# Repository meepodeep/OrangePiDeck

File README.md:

# ModuDeck

## A modular cyberdeck that supports multiple SBCS.
  - ### Modules
    - [Exoskeleton](##exoskeleton)
    -   [Compute Modules](##compute) 
        - [Pi 5](###pi-5)
        - [Pi zero 2 w](###pi-zero-2-w)
        - [Lattepanda Mu](###lattepanda-mu)
    - [Battery Modules](##battery)
      - [High Capacity](###2p4s)
      - [Low Capacity](###4s1p)
    - [Keyboard](##keyboard)
    - [Display](##display)
    - [How to assemble modules](##final-assembly)
  - [BOM](#bom) 
## What is the point
I set out to make a modular cyberdeck because I wanted to try to design something that doesnt follow the modern design trends of slimmer and less upgradeable and repairable computers. The modular concept helps alleviate these problems by making use of easily replaceable and upgradeable batteries and SBCs. This also solves the problem of many custom projects being very inconvenient to do maintenance on. For example, some people hotglue everything into place, making the project nearly impossible to work on. In this project, however, every part that you would need to replace is easily replaceable with m3 and m2.5 hardware, securing it in place. 

# Assembly Instructions
- ## Exoskeleton
  - ### Printing
1. Print Both main case peices vertically
2. Print both rear cases flat or vertically if you have elephants foot issues
3. Assemble both sides of each part together using either superglue, plastic welding, or your preferred method of attaching 3d prints.
4. Use m3 hardware to secure the back on once done with wiring exept leave these 3 holes unscrewed, they are for mounting the modules.
5. 
6. 

  - ### Wiring
1. Press fit all of the connectors including, HDMI, XT60, and the magnetic 4pin adafruit connector.

3. Solder the 12v supply for the xt60 on the battery to the 12v supply on the compute xt60 with 18awg wire.
4. Solder the 5v supply for the xt60 on the battery to the 5v supply on the compute xt60 with 18awg wire.

- ## Compute
  - ### Pi 5

1. Print the pi 5 compute model.
2. Assemble the cooler.
3. Solder 28awg wire to the 4 USB pins from the Bottom of the USB 2.0 connector on the set of pins closest to the edge of the board.
4. Remove the casing from the micro HDMI to HDMI adapter.
5. Press the HDMI into the casing.
6. Solder the 5v and gnd connections from the gpio to the + and - terminals onto an xt60 connector using 18awg wire. Press the connector into the 5v part of the module.

7. Press the 5v Xt60 into the case.
8. Solder the other ends of the wires coming from the USB to the magnetic connector in this order, from left to right, on the pin side. Ground, Data+, Data-, Vcc.
9. Press the Magnetic connector into the case.
10. Screw the pi into the mounting posts with m2.5 hardware.
  - ### Pi zero 2 w

1. Print the Pi Zero Compute model.
2. Assemble the cooler
3. Decase the USB hub.
4. Solder 28awg wire to the pins of the USB port at the end of the hub.
5. Solder the other ends of the wires coming from the USB to the magnetic connector in this order, from left to right, on the pin side. Ground, Data+, Data-, Vcc.
6. Press the Magnetic connector into the case.
7. Solder the 5V and GND connections from the GPIO to the + and - terminals onto an xt60 connector using 18awg wire.
8. Press the connector into the 5V part of the module.

9. Decase the mini HDMI adapter on the big HDMI side.
10. Press the HDMI into the case, and plug in the mini HDMI.
11. Screw the pi into the mounting posts with m2.5 hardware.
  - ### Lattepanda mu
1. Print the Lattepanda compute module.
2. Assemble the Panda, cooler, and devboard.
3. Desolder the Barrel jack connector
5. Solder 28awg wire to the 4 USB pins on the bottom of the furthest USB connector from the edge of the board on the port that is covered by the case.

6. Solder 18awg wire to the + and - of the barrel jack and solder them to the + and - of an xt60.
7. Press that into the 12V supply port on the module.
8. Solder the other ends of the wires coming from the USB to the magnetic connector in this order, from left to right, on the pin side. Ground, Data+, Data-, Vcc.
9. Desolder the hdmi port and solder 28awg magnet wire or normal wire onto each pin (i know its annoying) and also to the corresponding pins on the board, make these wires long enough to reach the other side of the case.
10. Press the HDMI port into the case.

- ## Battery
  - ### Build
1. Print battery module cover.
2. Print battery module.
  - ### 2p4s
    - Wiring
- # BEFORE DOING THIS MAKE SURE ALL OF THE CELLS ARE AT THE SAME VOLTAGE SO YOU DONT EXPLODE YOU HOUSE!!
1.  Wire 4 pairs of cells in a 1p configuration by spot welding nickel strips in between the cells.
2.  
3.  Wire all 4 of those 1p cells in series into a 2p4s Configuration by spot welding nickel strips, this is the green section of the diagram.
4.  Solder 5 equal-length wires of 22awg to the BMS and to the parts of the battery; these are the purple wires in the diagram.
5. 
6.  Solder a 12awg wire to the - terminal on the BMS.
7.  Solder a 12awg wire to the + terminal on the BMS and to the power switch, solder another 12awg wire to the other side of said switch, and press it into the case.
8.  
9.  Follow the wiring diagram from step 8 in order to complete the battery, then make sure to insulate all of the connections with your preferred method.
10.  Press both XT60s into their respective ports.
11.  Screw on the top using m3 hardware.
  - ### 4s1p
    - Same as 2p4s, but instead of having cell pairs, just use individual cells. 
- ## Keyboard
- 

1. Solder all of the switches onto the PCB.
2. Solder all of the diodes onto the PCB.
4. Solder the Pi Pico onto the bottom of the PCB.
5. Use [QMK Configurator](https://docs.qmk.fm/configurator_step_by_step) to configure and flash the board [here](https://config.qmk.fm/#/rart/rart75hs/LAYOUT_ansi_split_bs)
6.  Desolder the pi picos usb port.
7. Solder a 28awg wire onto each of the usb pads.
8. Solder the other ends of the wires coming from the USB to the magnetic connector in this order, from left to right, on the pin side vcc, Data-, Data+, Ground.
9. Press the magnetic connector into its slot where the compute module clips in.
10. 
11. Slide the keyboard in and screw it down using m3 hardware.
- ## Display
1. Print both screen mount halves and secure them together using ca plastic welding or your preferred adhesive.
2. Use double-sided tape to secure the driver board to the back of the screen on the left side, away from the compute module.
3. Position the screen in the main case and put the scren mount around it aligned with the screw holes.
4. Screw in m3 hardware from the top of the case in all of the holes.
5. Plug the HDMI coming from the compute module bay into the display board.
6. Use 18awg wire to the 12V XT60 from the battery module bay to the power pads on the driver board after desoldering the barrel plug.
- ## Final Assembly
1. Slot the compute module into the left of the cyberdeck making sure all of the connectors line up.
2. Use 2 m3 bolts to secure the module in place.
3. 
4. Slot the battery in, turned off, into the slot on the right, making sure all of the connectors line up.
5. Screw in one m3 bolt to secure it in place
6. 

# BOM

| Item |	Quantity |	Total price+Shipping | Use In project	| Item Source
| ------------- | ------------- | ------------- | ------------- |------------- |
| General |||||			
| Display |	x1 |	$64.19 |	displays | https://www.ebay.com/itm/145841358470? |
| m3 hardware kit |	x1	| $7.99|	Mount most things	| https://www.amazon.com/Hincell-540pcs-Button-Washers-Stainless/dp/B0D1CV8V9Y?source=ps-sl-shoppingads-lpcontext&ref_=fplfs&smid=A8FI3NPCLLLAU&gQT=2&th=1|
|m2.5 4mm |	x1 |	$1.86 |	mount the pis if you use them |	https://www.aliexpress.us/item/3256805692588351.html?spm=a2g0o.productlist.main.9.70f8PGXgPGXgES&algo_pvid=f41aab01-f6bc-4ebf-8b6a-e709e2d91d9e&algo_exp_id=f41aab01-f6bc-4ebf-8b6a-e709e2d91d9e-8&pdp_ext_f=%7B%22order%22%3A%22141%22%2C%22eval%22%3A%221%22%7D&pdp_npi=4%40dis%21USD%212.63%212.63%21%21%212.63%212.63%21%402101c67a17493315079284241e4c88%2112000034678326960%21sea%21US%214381910819%21X&curPageLogUid=wPZG0AeXcYEt&utparam-url=scene%3Asearch%7Cquery_from%3A|
|18awg wire	| x1 |	$13.76 | most wiring |	https://www.amazon.com/Nilight-Electrical-Conductor-Extension-Amplifier/dp/B0CYZPW42Q?source=ps-sl-shoppingads-lpcontext&ref_=fplfs&smid=ATVPDKIKX0DER&gQT=1&th=1 |
|28awg wire	| x1 |	$7.99 |	Usb wiring |	https://www.amazon.com/Fermerry-Stranded-Silicone-Cables-Electrical/dp/B089CR4SDM?source=ps-sl-shoppingads-lpcontext&ref_=fplfs&smid=AMHYOXF0C8EDF&gQT=1&th=1 |
|12awg wire |	x1 |	$3.94 |	Battery wires |	https://www.aliexpress.us/item/3256807129117447.html?spm=a2g0o.productlist.main.3.7ab0a156NrdRf6&algo_pvid=3e03f551-26de-40a9-8a5d-b5bc81856425&algo_exp_id=3e03f551-26de-40a9-8a5d-b5bc81856425-2&pdp_ext_f=%7B%22order%22%3A%223673%22%2C%22eval%22%3A%221%22%7D&pdp_npi=4%40dis%21USD%216.91%213.94%21%21%2149.31%2128.11%21%402101c5b117493323478534303ed134%2112000040296899199%21sea%21US%214381910819%21X&curPageLogUid=HZUS3mRJr7EU&utparam-url=scene%3Asearch%7Cquery_from%3A|
|Filament	| x1 |	$20 |	be every printed part |	Idk wherever you get filament |
|xt60s	| x1 |	$8.99 |	be every printed part |	[amazon](https://www.amazon.com/Amass-Bullet-Connector-Upgrated-Sheath/dp/B074PN6N4K?source=ps-sl-shoppingads-lpcontext&ref_=fplfs&smid=A1JGQIWP459RKC&gQT=2&th=1) |
|Magnetic Connectors| x1 | $$3.67 | Connect usb |https://www.aliexpress.us/item/3256805098127227.html?spm=a2g0o.productlist.main.5.2ae010ecQ0TgsU&algo_pvid=55902741-ef7a-41f4-bcef-df4c2733f685&algo_exp_id=55902741-ef7a-41f4-bcef-df4c2733f685-4&pdp_ext_f=%7B%22order%22%3A%22273%22%2C%22eval%22%3A%221%22%7D&pdp_npi=4%40dis%21USD%213.53%213.53%21%21%2125.20%2125.20%21%402101d9ef17496563895162555efc36%2112000046387602811%21sea%21US%214381910819%21X&curPageLogUid=tgn8R5EbU7zs&utparam-url=scene%3Asearch%7Cquery_from%3A|
|Nickel strip| x1| $5.69 | build batteries| https://www.amazon.com/MECCANIXITY-Nickel-Battery-Soldering-Welding/dp/B0CVXLLGCQ?source=ps-sl-shoppingads-lpcontext&ref_=fplfs&smid=A1NR50YASSZD11&gQT=1&th=1|
|Total|| $138.08 |||
||||||
|Keyboard Parts	| | | | |	
|Pi pico |	x1 |	$4 |	drive the keyboard | https://www.adafruit.com/product/4864 |
|Keyboard pcb	| x5 |	$35.47 |	Be a keyboard PCB |	PCBWAY |
|Gateron Red	| x100	| $34.40 |	Be switches |	https://www.aliexpress.us/item/3256805905674117 |
|Keycaps |	x80 |	$14.16 |	Be keycaps |	https://www.aliexpress.us/item/3256807292808339.html? |
|Shipping |	$6.99	| | | |
|Total | |$95 | | |		
||||||
|Battery Module 2p4s |||||				
|DC-DC converter |	x2 |	$25.60 |	Convert the battery voltage to 12v/5v |	https://www.dfrobot.com/product-2599.html |
|18650s | x8 |	$29.28 |	be batteries |	https://www.18650batterystore.com/products/samsung-25r-18650?variant=37119890063511 |
|Bms |	x1 |	$1.75 |	be a bms for the batteries |	https://www.aliexpress.us/item/ |
|RA11131121 |	x1 |	$0.69 |	power switch |	https://www.mouser.com/ProductDetail/E-Switch/RA11131121?qs=QtyuwXswaQhes8SRTBHYHQ%3D%3D&mgh=1&gQT=1 |
|373 |	x1 |	$0.95 |	charger |	https://www.mouser.com/ProductDetail/Adafruit/373?qs=GURawfaeGuDDC%2FyE6Usrdw%3D%3D |
|Total| |	$58.27 | | |	
|Battery Module 4s1p |||||	
|DC-DC converter |	x2 |	$25.60 |	Convert the battery voltage to 12v/5v |	https://www.dfrobot.com/product-2599.html |
|18650s | 	x4 |	$18.59 |	be batteries |	https://www.18650batterystore.com/products/samsung-25r-18650?variant=37119890063511 |
|Bms |	x1 |	$1.75 |	be a bms for the batteries |	https://www.aliexpress.us/item/ |
|RA11131121 |	x1 |	$3.26 |	power switch |	https://www.aliexpress.us/item/3256808591861621.html?spm=a2g0o.productlist.main.4.bbaa3f0amP9fEs&aem_p4p_detail=202506110835012802225516499430001432280&algo_pvid=22d13a10-315a-4e88-a7fb-5fc6e3a68f98&algo_exp_id=22d13a10-315a-4e88-a7fb-5fc6e3a68f98-3&pdp_ext_f=%7B%22order%22%3A%22115%22%2C%22eval%22%3A%221%22%7D&pdp_npi=4%40dis%21USD%212.08%211.06%21%21%2114.86%217.57%21%402101c67a17496561013444578ee284%2112000046629830173%21sea%21US%214381910819%21X&curPageLogUid=AIpxTC6KBWSG&utparam-url=scene%3Asearch%7Cquery_from%3A&search_p4p_id=202506110835012802225516499430001432280_1 |
|Total | | $49.20 |	| |	
||||||
|Pi zero 2 w compute | | | | |
|pi zero 2 w	| x1 |	$23.00 |	Main computer |	https://www.adafruit.com/product/5291 |
|mini hdmi to hdmi adapter |	x1 |	$6.99 |	adapt the HDMI |	https://www.amazon.com/Micro-Adapter-Female-Support-Raspberry/dp/B09HS74STL?source=ps-sl-shoppingads-lpcontext&ref_=fplfs&psc=1&smid=A1NY347U90KP9S&gQT=1 |
| USB hub and pi cooloer	| x1 |	$9.99 |	Cool the pi and breakout usb |	https://www.amazon.com/Raspberry-iUniker-Aluminum-Passive-Adapter/dp/B09XK36QNB/140-2177712-4060064?pd_rd_w=vyCyv&content-id=amzn1.sym.4c8c52db-06f8-4e42-8e56-912796f2ea6c&pf_rd_p=4c8c52db-06f8-4e42-8e56-912796f2ea6c&pf_rd_r=MV80K33AW3WARSHK5YW9&pd_rd_wg=EWgEt&pd_rd_r=25190511-4df9-42d1-908e-41de3ecdd1ec&pd_rd_i=B09XK36QNB&psc=1 |
|Total |	| $39.98 |	| | |	
||||||	
|Pi 5 Compute | | | | |
|Pi 5 8gb |	x1 |	$96.98 |	main computer |	https://www.pishop.us/product/raspberry-pi-5-8gb/?searchid=0&search_query=pi+5|
|Micro HDMI to Standard HDMI |	x1 |	$4.25 |	hdmi adapter |	https://www.pishop.us/product/micro-hdmi-to-standard-hdmi-adapter-white/|
|Cooler	| x1 |	$8.95 |	cool the pi |	https://www.pishop.us/product/dedicated-all-in-one-aluminum-cooler-for-raspberry-pi-5-pwm/?searchid=0&search_query=pi5+cooler|
|Total | | $110.18 | | |	
||||||
|Lattepanda Mu Compute| | | | |	
|Lattepanda Mu with lite carrier and active cooler |	x1 |	$220.00 |	main computer |	https://www.dfrobot.com/kit-004.html|
|Total| |	$220.00| | |

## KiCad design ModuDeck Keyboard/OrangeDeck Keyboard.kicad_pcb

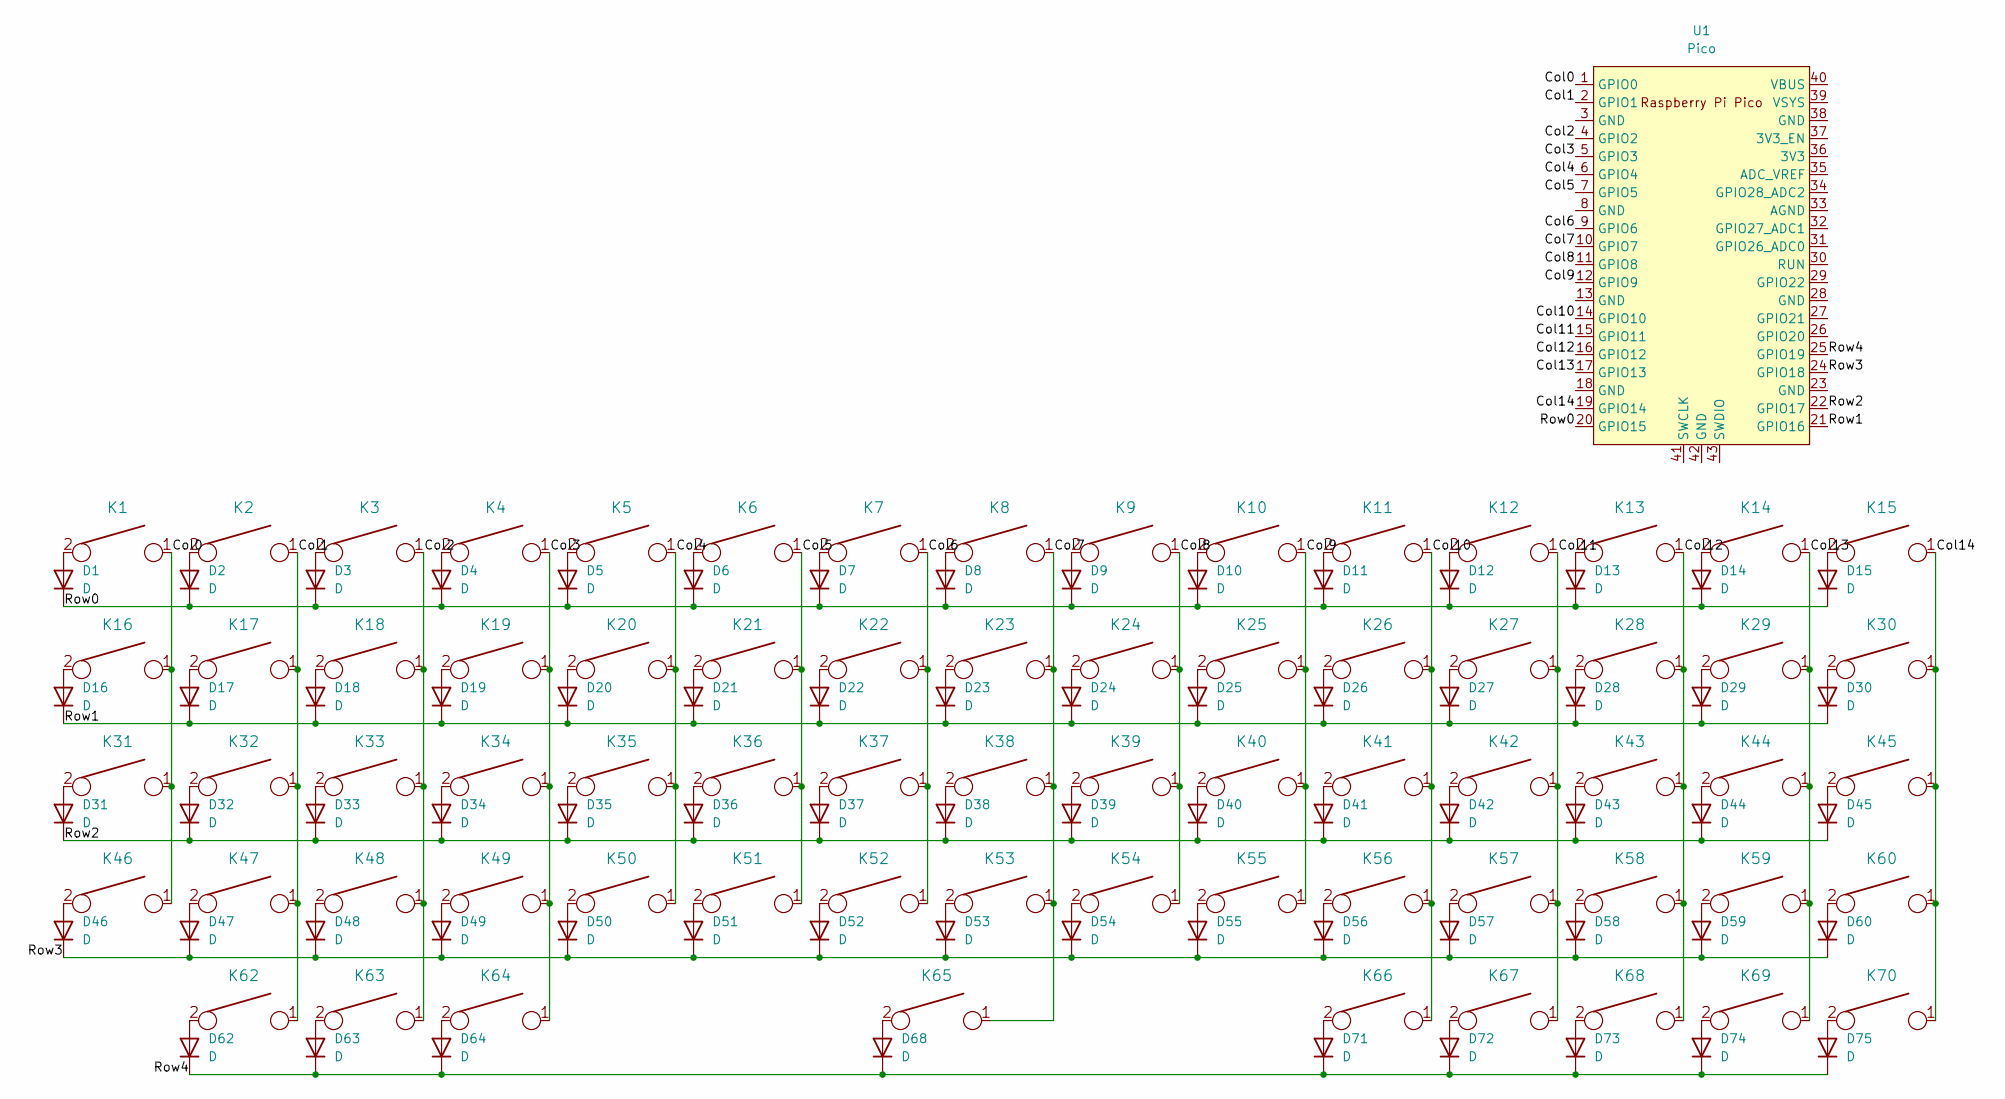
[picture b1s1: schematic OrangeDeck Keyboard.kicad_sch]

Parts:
D1, D2, D3, D4, D5, D6, D7, D8, D9, D10, D11, D12, D13, D14, D15, D16, D17, D18, D19, D20, D21, D22, D23, D24, D25, D26, D27, D28, D29, D30, D31, D32, D33, D34, D35, D36, D37, D38, D39, D40, D41, D42, D43, D44, D45, D46, D47, D48, D49, D50, D51, D52, D53, D54, D55, D56, D57, D58, D59, D60, D62, D63, D64, D68, D71, D72, D73, D74, D75: D; D_SOD123_axial
K1, K2, K3, K4, K5, K6, K7, K8, K9, K10, K11, K12, K13, K14, K15, K16, K17, K18, K19, K20, K21, K22, K23, K24, K25, K26, K27, K28, K29, K30, K31, K32, K33, K34, K35, K36, K37, K38, K39, K40, K41, K42, K43, K44, K45, K46, K47, K48, K49, K50, K51, K52, K53, K54, K55, K56, K57, K58, K59, K60, K62, K63, K64, K66, K67, K68, K69, K70: KEYSW; Mx_Alps_100
K65: KEYSW; Mx_Alps_625
U1: Pico; RPi_Pico_SMD_TH

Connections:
/Col0: K1.1, K16.1, K31.1, K46.1, U1.1 (GPIO0)
/Col1: K2.1, K17.1, K32.1, K47.1, K62.1, U1.2 (GPIO1)
/Col2: K3.1, K18.1, K33.1, K48.1, K63.1, U1.4 (GPIO2)
/Col3: K4.1, K19.1, K34.1, K49.1, K64.1, U1.5 (GPIO3)
/Col4: K5.1, K20.1, K35.1, K50.1, U1.6 (GPIO4)
/Col5: K6.1, K21.1, K36.1, K51.1, U1.7 (GPIO5)
/Col6: K7.1, K22.1, K37.1, K52.1, U1.9 (GPIO6)
/Col7: K8.1, K23.1, K38.1, K53.1, K65.1, U1.10 (GPIO7)
/Col8: K9.1, K24.1, K39.1, K54.1, U1.11 (GPIO8)
/Col9: K10.1, K25.1, K40.1, K55.1, U1.12 (GPIO9)
/Col10: K11.1, K26.1, K41.1, K56.1, K66.1, U1.14 (GPIO10)
/Col11: K12.1, K27.1, K42.1, K57.1, K67.1, U1.15 (GPIO11)
/Col12: K13.1, K28.1, K43.1, K58.1, K68.1, U1.16 (GPIO12)
/Col13: K14.1, K29.1, K44.1, K59.1, K69.1, U1.17 (GPIO13)
/Col14: K15.1, K30.1, K45.1, K60.1, K70.1, U1.19 (GPIO14)
/Row0: D1.1 (K), D2.1 (K), D3.1 (K), D4.1 (K), D5.1 (K), D6.1 (K), D7.1 (K), D8.1 (K), D9.1 (K), D10.1 (K), D11.1 (K), D12.1 (K), D13.1 (K), D14.1 (K), D15.1 (K), U1.20 (GPIO15)
/Row1: D16.1 (K), D17.1 (K), D18.1 (K), D19.1 (K), D20.1 (K), D21.1 (K), D22.1 (K), D23.1 (K), D24.1 (K), D25.1 (K), D26.1 (K), D27.1 (K), D28.1 (K), D29.1 (K), D30.1 (K), U1.21 (GPIO16)
/Row2: D31.1 (K), D32.1 (K), D33.1 (K), D34.1 (K), D35.1 (K), D36.1 (K), D37.1 (K), D38.1 (K), D39.1 (K), D40.1 (K), D41.1 (K), D42.1 (K), D43.1 (K), D44.1 (K), D45.1 (K), U1.22 (GPIO17)
/Row3: D46.1 (K), D47.1 (K), D48.1 (K), D49.1 (K), D50.1 (K), D51.1 (K), D52.1 (K), D53.1 (K), D54.1 (K), D55.1 (K), D56.1 (K), D57.1 (K), D58.1 (K), D59.1 (K), D60.1 (K), U1.24 (GPIO18)
/Row4: D62.1 (K), D63.1 (K), D64.1 (K), D68.1 (K), D71.1 (K), D72.1 (K), D73.1 (K), D74.1 (K), D75.1 (K), U1.25 (GPIO19)
unnamed: D1.2 (A), K1.2
unnamed: D2.2 (A), K2.2
unnamed: D3.2 (A), K3.2
unnamed: D4.2 (A), K4.2
unnamed: D5.2 (A), K5.2
unnamed: D6.2 (A), K6.2
unnamed: D7.2 (A), K7.2
unnamed: D8.2 (A), K8.2
unnamed: D9.2 (A), K9.2
unnamed: D10.2 (A), K10.2
unnamed: D11.2 (A), K11.2
unnamed: D12.2 (A), K12.2
unnamed: D13.2 (A), K13.2
unnamed: D14.2 (A), K14.2
unnamed: D15.2 (A), K15.2
unnamed: D16.2 (A), K16.2
unnamed: D17.2 (A), K17.2
unnamed: D18.2 (A), K18.2
unnamed: D19.2 (A), K19.2
unnamed: D20.2 (A), K20.2
unnamed: D21.2 (A), K21.2
unnamed: D22.2 (A), K22.2
unnamed: D23.2 (A), K23.2
unnamed: D24.2 (A), K24.2
unnamed: D25.2 (A), K25.2
unnamed: D26.2 (A), K26.2
unnamed: D27.2 (A), K27.2
unnamed: D28.2 (A), K28.2
unnamed: D29.2 (A), K29.2
unnamed: D30.2 (A), K30.2
unnamed: D31.2 (A), K31.2
unnamed: D32.2 (A), K32.2
unnamed: D33.2 (A), K33.2
unnamed: D34.2 (A), K34.2
unnamed: D35.2 (A), K35.2
unnamed: D36.2 (A), K36.2
unnamed: D37.2 (A), K37.2
unnamed: D38.2 (A), K38.2
unnamed: D39.2 (A), K39.2
unnamed: D40.2 (A), K40.2
unnamed: D41.2 (A), K41.2
unnamed: D42.2 (A), K42.2
unnamed: D43.2 (A), K43.2
unnamed: D44.2 (A), K44.2
unnamed: D45.2 (A), K45.2
unnamed: D46.2 (A), K46.2
unnamed: D47.2 (A), K47.2
unnamed: D48.2 (A), K48.2
unnamed: D49.2 (A), K49.2
unnamed: D50.2 (A), K50.2
unnamed: D51.2 (A), K51.2
unnamed: D52.2 (A), K52.2
unnamed: D53.2 (A), K53.2
unnamed: D54.2 (A), K54.2
unnamed: D55.2 (A), K55.2
unnamed: D56.2 (A), K56.2
unnamed: D57.2 (A), K57.2
unnamed: D58.2 (A), K58.2
unnamed: D59.2 (A), K59.2
unnamed: D60.2 (A), K60.2
unnamed: D62.2 (A), K62.2
unnamed: D63.2 (A), K63.2
unnamed: D64.2 (A), K64.2
unnamed: D68.2 (A), K65.2
unnamed: D71.2 (A), K66.2
unnamed: D72.2 (A), K67.2
unnamed: D73.2 (A), K68.2
unnamed: D74.2 (A), K69.2
unnamed: D75.2 (A), K70.2

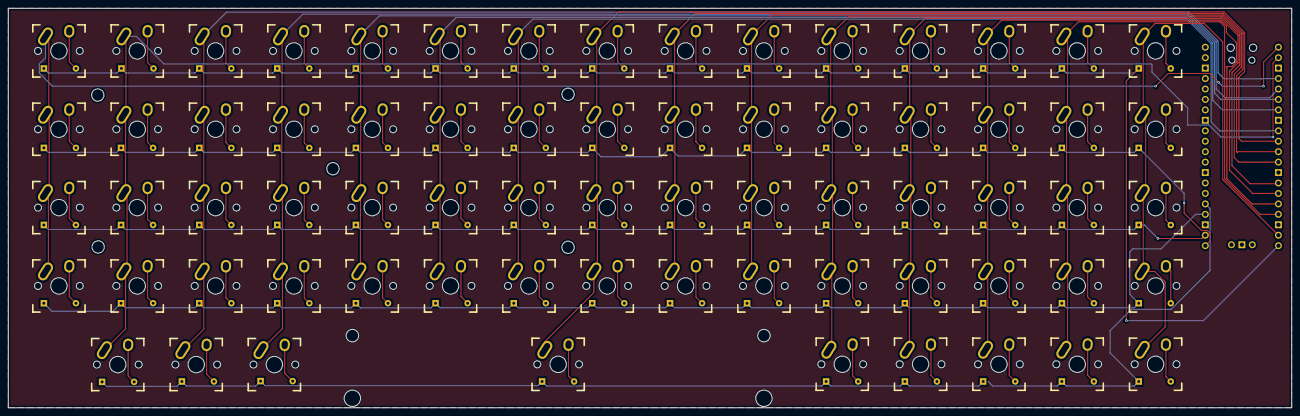
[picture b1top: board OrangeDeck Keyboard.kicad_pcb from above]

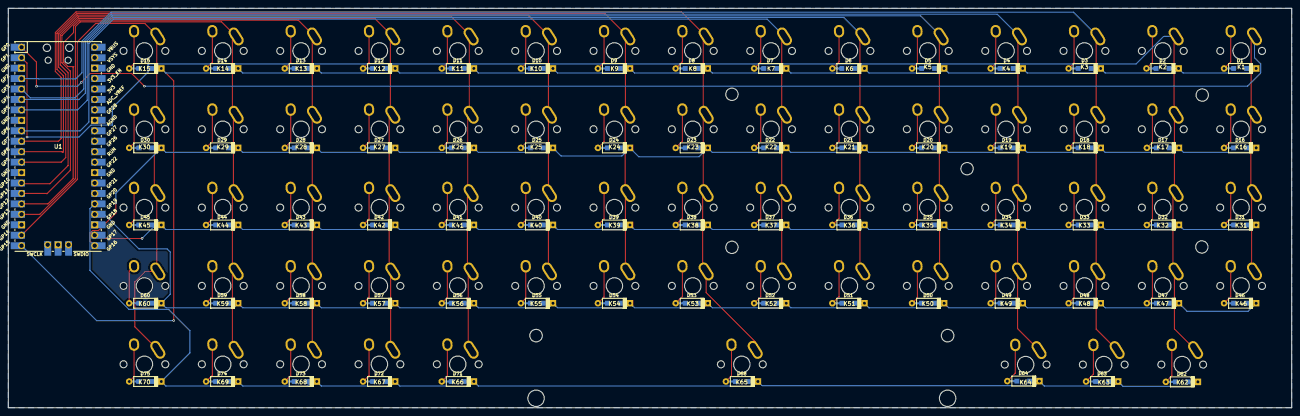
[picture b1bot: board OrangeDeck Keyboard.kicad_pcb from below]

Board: 2 copper layers, 312.1 x 97.1 mm, 139 parts (70 on the bottom side), 89 nets.

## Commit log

2025-06-03 adding all my work lol
2025-06-06 Finished battery guides
2025-06-07 Finished instructions
2025-06-07 fixed mounting
2025-06-13 fixing ports
2025-06-13 wawwa
2025-06-13 wawa
2025-06-15 edited stls
